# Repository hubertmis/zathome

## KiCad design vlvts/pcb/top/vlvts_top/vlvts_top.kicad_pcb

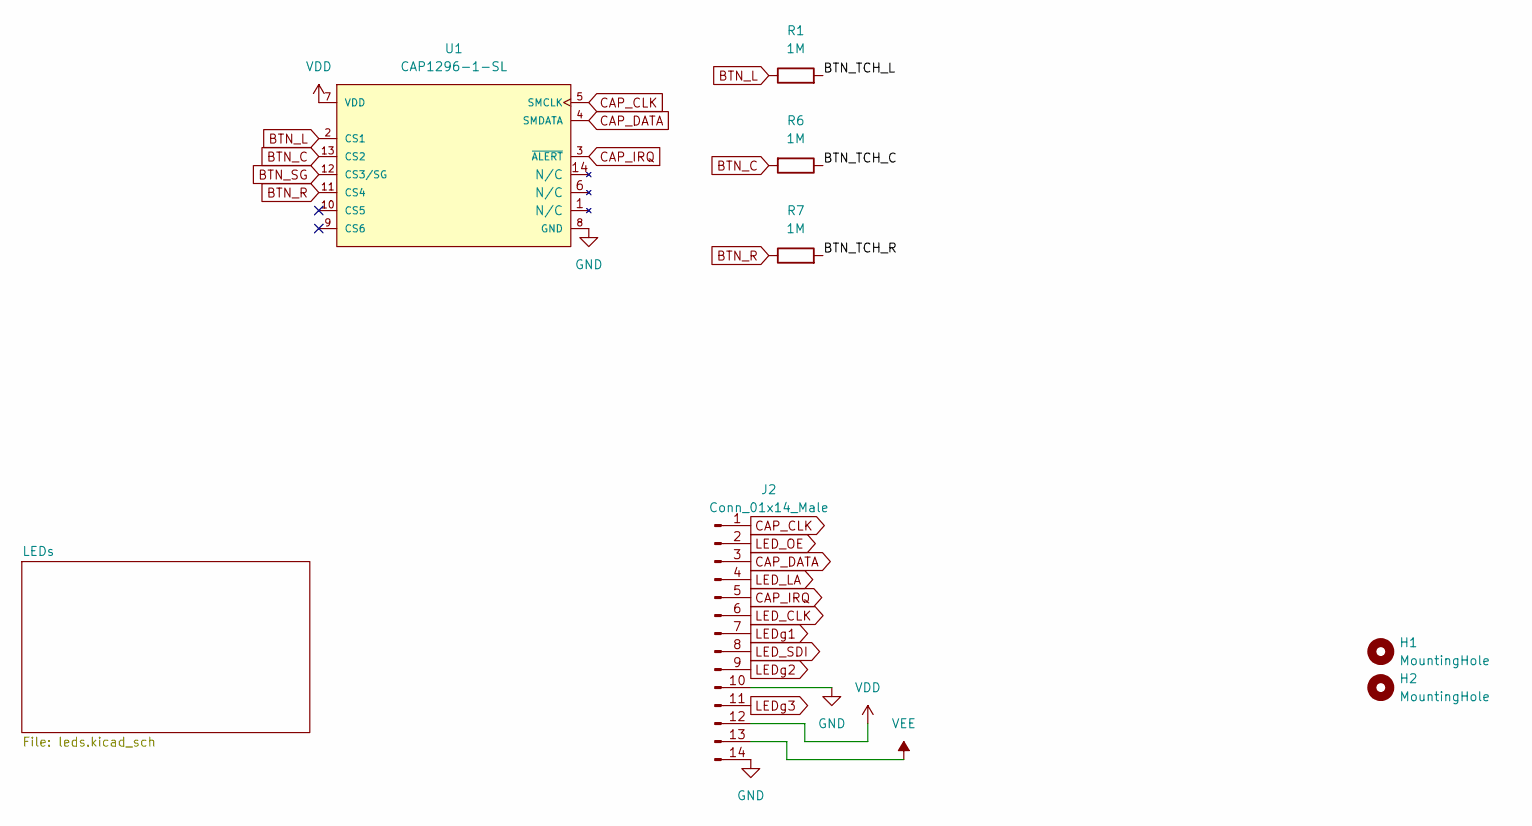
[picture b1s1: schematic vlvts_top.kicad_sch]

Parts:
H1, H2: MountingHole; MountingHole_3.2mm_M3_DIN965
J2: Conn_01x14_Male; PinHeader_2x07_P1.27mm_Vertical_SMD
R1, R6, R7: 1M; R_0603_1608Metric_Pad0.98x0.95mm_HandSolder
U1: CAP1296-1-SL; SOIC-14_3.9x8.7mm_P1.27mm

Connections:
/BTN_TCH_C: R6.1
/BTN_TCH_L: R1.2
/BTN_TCH_R: R7.2
BTN_C: R6.2, U1.13 (CS2)
BTN_L: R1.1, U1.2 (CS1)
BTN_R: R7.1, U1.11 (CS4)
BTN_SG: U1.12 (CS3/SG)
CAP_CLK: J2.1, U1.5 (SMCLK)
CAP_DATA: J2.3, U1.4 (SMDATA)
CAP_IRQ: J2.5, U1.3 (~ALERT)
GND: J2.10, J2.14, U1.8 (GND); also elsewhere on the board
LED_CLK: J2.6; also elsewhere on the board
LED_LA: J2.4; also elsewhere on the board
LED_OE: J2.2; also elsewhere on the board
LED_SDI: J2.8; also elsewhere on the board
LEDg1: J2.7; also elsewhere on the board
LEDg2: J2.9; also elsewhere on the board
LEDg3: J2.11; also elsewhere on the board
VDD: J2.12, U1.7 (VDD)
VEE: J2.13; also elsewhere on the board

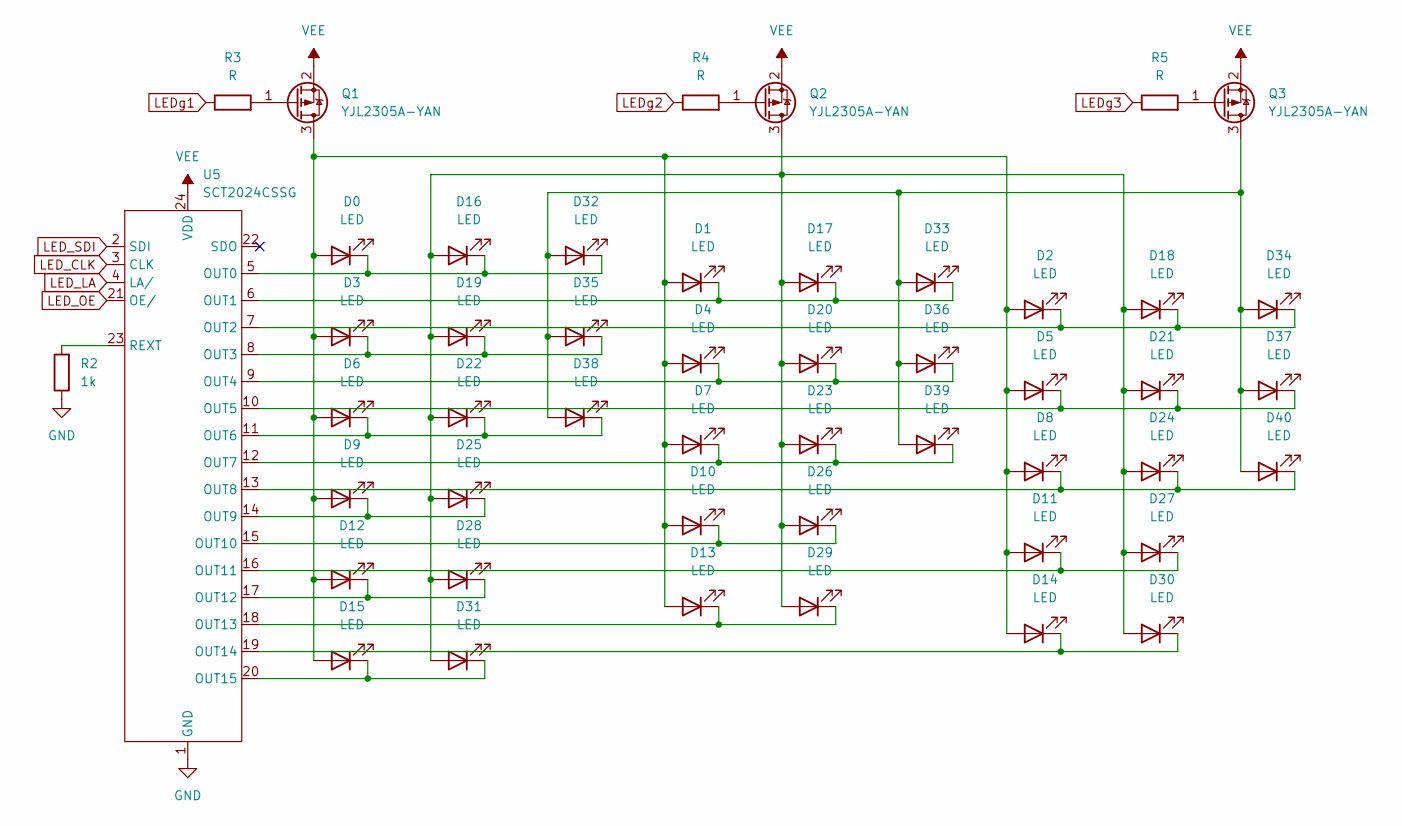
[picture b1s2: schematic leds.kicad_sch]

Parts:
D0, D1, D2, D3, D4, D5, D6, D7, D8, D9, D10, D11, D12, D13, D14, D15, D16, D17, D18, D19, D20, D21, D22, D23, D24, D25, D26, D27, D28, D29, D30, D31, D32, D33, D34, D35, D36, D37, D38, D39, D40: LED; LED_0603_1608Metric_Pad1.05x0.95mm_HandSolder
Q1, Q2, Q3: YJL2305A-YAN; SOT-23
R2: 1k; R_0603_1608Metric_Pad0.98x0.95mm_HandSolder
R3, R4, R5: R; R_0603_1608Metric_Pad0.98x0.95mm_HandSolder
U5: SCT2024CSSG; SSOP-24_3.9x8.7mm_P0.635mm

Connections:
GND: R2.1, U5.1 (GND); also elsewhere on the board
LED_CLK: U5.3 (CLK); also elsewhere on the board
LED_LA: U5.4 (LA/); also elsewhere on the board
LED_OE: U5.21 (OE/); also elsewhere on the board
LED_SDI: U5.2 (SDI); also elsewhere on the board
LEDg1: R3.1; also elsewhere on the board
LEDg2: R4.1; also elsewhere on the board
LEDg3: R5.1; also elsewhere on the board
unnamed: D0.2 (A), D1.2 (A), D2.2 (A), D3.2 (A), D4.2 (A), D5.2 (A), D6.2 (A), D7.2 (A), D8.2 (A), D9.2 (A), D10.2 (A), D11.2 (A), D12.2 (A), D13.2 (A), D14.2 (A), D15.2 (A), Q1.3 (D)
unnamed: D0.1 (K), D16.1 (K), D32.1 (K), U5.5 (OUT0)
unnamed: D1.1 (K), D17.1 (K), D33.1 (K), U5.6 (OUT1)
unnamed: D10.1 (K), D26.1 (K), U5.15 (OUT10)
unnamed: D11.1 (K), D27.1 (K), U5.16 (OUT11)
unnamed: D12.1 (K), D28.1 (K), U5.17 (OUT12)
unnamed: D13.1 (K), D29.1 (K), U5.18 (OUT13)
unnamed: D14.1 (K), D30.1 (K), U5.19 (OUT14)
unnamed: D15.1 (K), D31.1 (K), U5.20 (OUT15)
unnamed: D16.2 (A), D17.2 (A), D18.2 (A), D19.2 (A), D20.2 (A), D21.2 (A), D22.2 (A), D23.2 (A), D24.2 (A), D25.2 (A), D26.2 (A), D27.2 (A), D28.2 (A), D29.2 (A), D30.2 (A), D31.2 (A), Q2.3 (D)
unnamed: D2.1 (K), D18.1 (K), D34.1 (K), U5.7 (OUT2)
unnamed: D3.1 (K), D19.1 (K), D35.1 (K), U5.8 (OUT3)
unnamed: D4.1 (K), D20.1 (K), D36.1 (K), U5.9 (OUT4)
unnamed: D5.1 (K), D21.1 (K), D37.1 (K), U5.10 (OUT5)
unnamed: D6.1 (K), D22.1 (K), D38.1 (K), U5.11 (OUT6)
unnamed: D7.1 (K), D23.1 (K), D39.1 (K), U5.12 (OUT7)
unnamed: D8.1 (K), D24.1 (K), D40.1 (K), U5.13 (OUT8)
unnamed: D9.1 (K), D25.1 (K), U5.14 (OUT9)
unnamed: D32.2 (A), D33.2 (A), D34.2 (A), D35.2 (A), D36.2 (A), D37.2 (A), D38.2 (A), D39.2 (A), D40.2 (A), Q3.3 (D)
unnamed: Q1.1 (G), R3.2
unnamed: Q2.1 (G), R4.2
unnamed: Q3.1 (G), R5.2
unnamed: R2.2, U5.23 (REXT)
VEE: Q1.2 (S), Q2.2 (S), Q3.2 (S), U5.24 (VDD); also elsewhere on the board

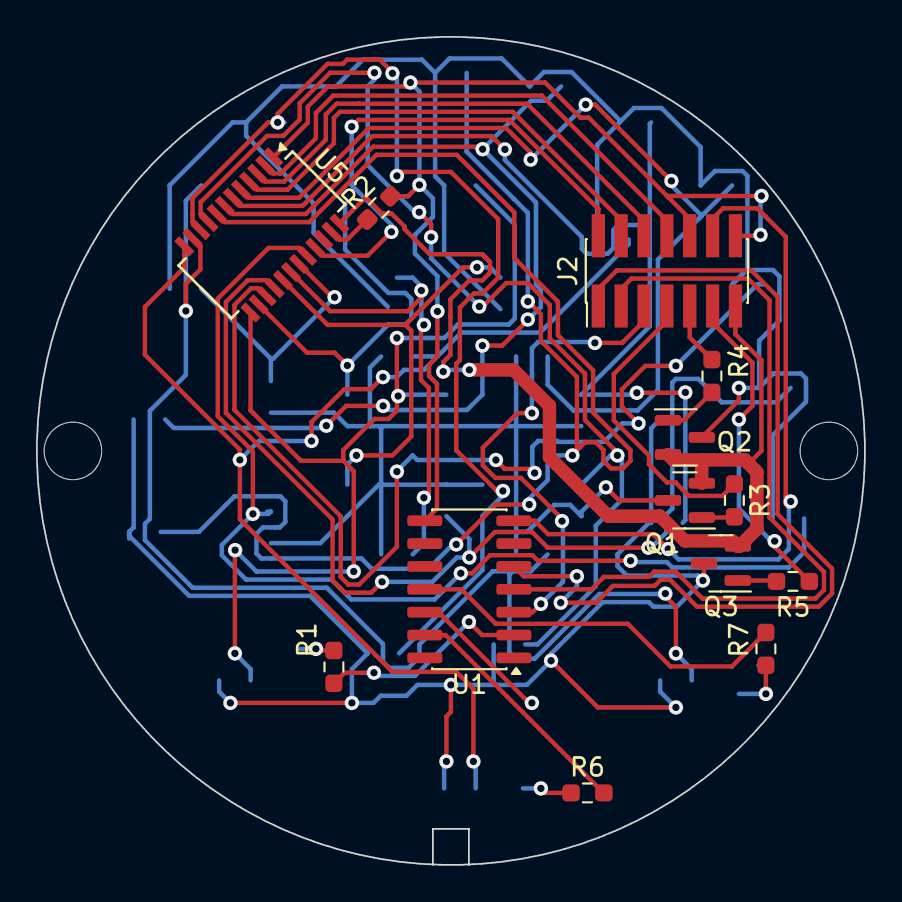
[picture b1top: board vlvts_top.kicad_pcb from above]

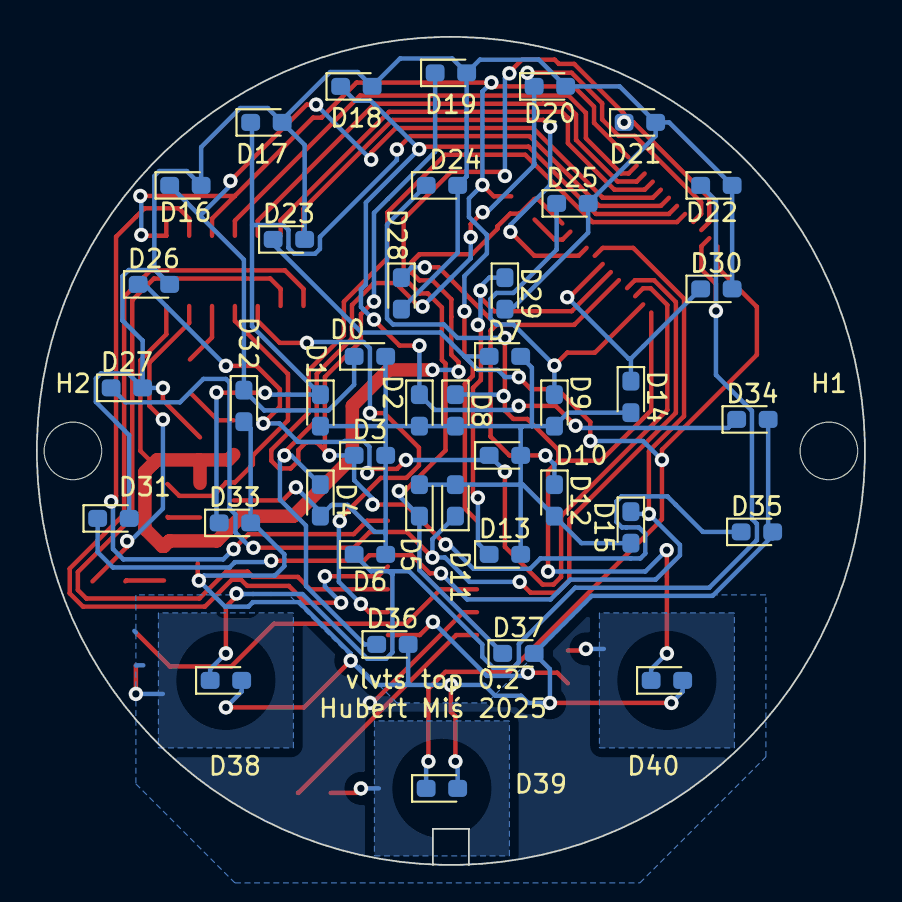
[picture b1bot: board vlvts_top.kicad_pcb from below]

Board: 2 copper layers, 46.0 x 46.0 mm, 56 parts (43 on the bottom side), 39 nets.

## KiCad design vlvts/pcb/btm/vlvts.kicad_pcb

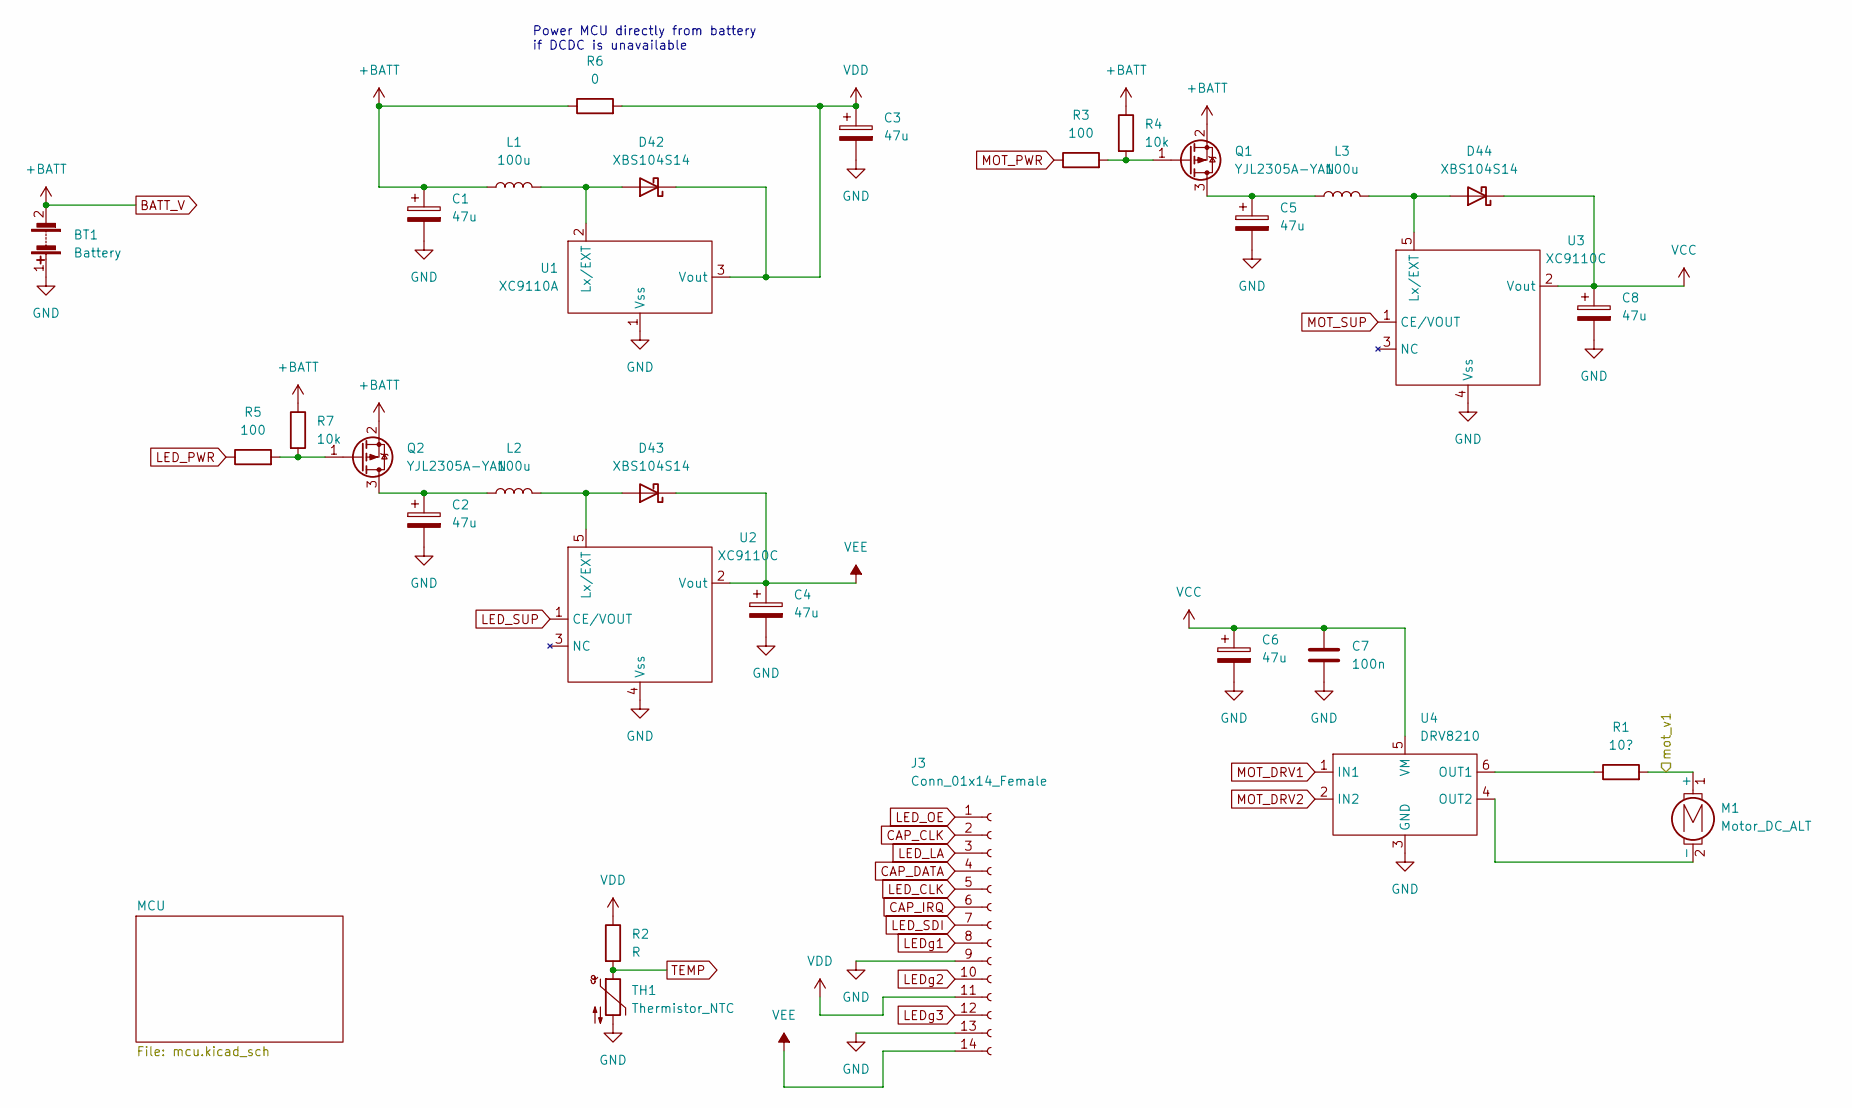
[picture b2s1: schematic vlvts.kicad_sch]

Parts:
BT1: Battery; JST_PH_B2B-PH-SM4-TB_1x02-1MP_P2.00mm_Vertical
C1, C2, C3, C4, C5, C6, C8: 47u; CP_EIA-6032-28_Kemet-C_Pad2.25x2.35mm_HandSolder
C7: 100n; C_0603_1608Metric_Pad1.08x0.95mm_HandSolder
D42, D43, D44: XBS104S14; D_SOD-123
J3: Conn_01x14_Female; PinHeader_2x07_P1.27mm_Vertical
L1, L2, L3: 100u; L_0805_2012Metric_Pad1.05x1.20mm_HandSolder
M1: Motor_DC_ALT; JST_PH_B2B-PH-SM4-TB_1x02-1MP_P2.00mm_Vertical
Q1, Q2: YJL2305A-YAN; SOT-23
R1: 10?; R_0805_2012Metric_Pad1.20x1.40mm_HandSolder
R2: R; R_0603_1608Metric_Pad0.98x0.95mm_HandSolder
R3, R5: 100; R_0603_1608Metric_Pad0.98x0.95mm_HandSolder
R4, R7: 10k; R_0603_1608Metric_Pad0.98x0.95mm_HandSolder
R6: 0; R_0603_1608Metric_Pad0.98x0.95mm_HandSolder
TH1: Thermistor_NTC; R_Axial_DIN0207_L6.3mm_D2.5mm_P2.54mm_Vertical
U1: XC9110A; SOT-23
U2, U3: XC9110C; SOT-23-5
U4: DRV8210; SOT-563

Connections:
/mot_v1: M1.1 (+), R1.2
BATT_V: BT1.2 (-), C1.1, L1.1, Q1.2 (S), Q2.2 (S), R4.1, R6.1, R7.1; also elsewhere on the board
CAP_CLK: J3.2; also elsewhere on the board
CAP_DATA: J3.4; also elsewhere on the board
CAP_IRQ: J3.6; also elsewhere on the board
GND: BT1.1 (+), C1.2, C2.2, C3.2, C4.2, C5.2, C6.2, C7.2, C8.2, J3.9, J3.13, TH1.2, U1.1 (Vss), U2.4 (Vss), U3.4 (Vss), U4.3 (GND); also elsewhere on the board
LED_CLK: J3.5; also elsewhere on the board
LED_LA: J3.3; also elsewhere on the board
LED_OE: J3.1; also elsewhere on the board
LED_PWR: R5.1; also elsewhere on the board
LED_SDI: J3.7; also elsewhere on the board
LED_SUP: U2.1 (CE/VOUT); also elsewhere on the board
LEDg1: J3.8; also elsewhere on the board
LEDg2: J3.10; also elsewhere on the board
LEDg3: J3.12; also elsewhere on the board
MOT_DRV1: U4.1 (IN1); also elsewhere on the board
MOT_DRV2: U4.2 (IN2); also elsewhere on the board
MOT_PWR: R3.1; also elsewhere on the board
MOT_SUP: U3.1 (CE/VOUT); also elsewhere on the board
unnamed: D42.2 (A), L1.2, U1.2 (Lx/EXT)
unnamed: D43.2 (A), L2.2, U2.5 (Lx/EXT)
unnamed: D44.2 (A), L3.2, U3.5 (Lx/EXT)
unnamed: M1.2 (-), U4.4 (OUT2)
unnamed: C5.1, L3.1, Q1.3 (D)
unnamed: Q1.1 (G), R3.2, R4.2
unnamed: C2.1, L2.1, Q2.3 (D)
unnamed: Q2.1 (G), R5.2, R7.2
unnamed: R1.1, U4.6 (OUT1)
TEMP: R2.2, TH1.1; also elsewhere on the board
VCC: C6.1, C7.1, C8.1, D44.1 (K), U3.2 (Vout), U4.5 (VM)
VDD: C3.1, D42.1 (K), J3.11, R2.1, R6.2, U1.3 (Vout); also elsewhere on the board
VEE: C4.1, D43.1 (K), J3.14, U2.2 (Vout)

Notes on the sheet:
Power MCU directly from battery if DCDC is unavailable

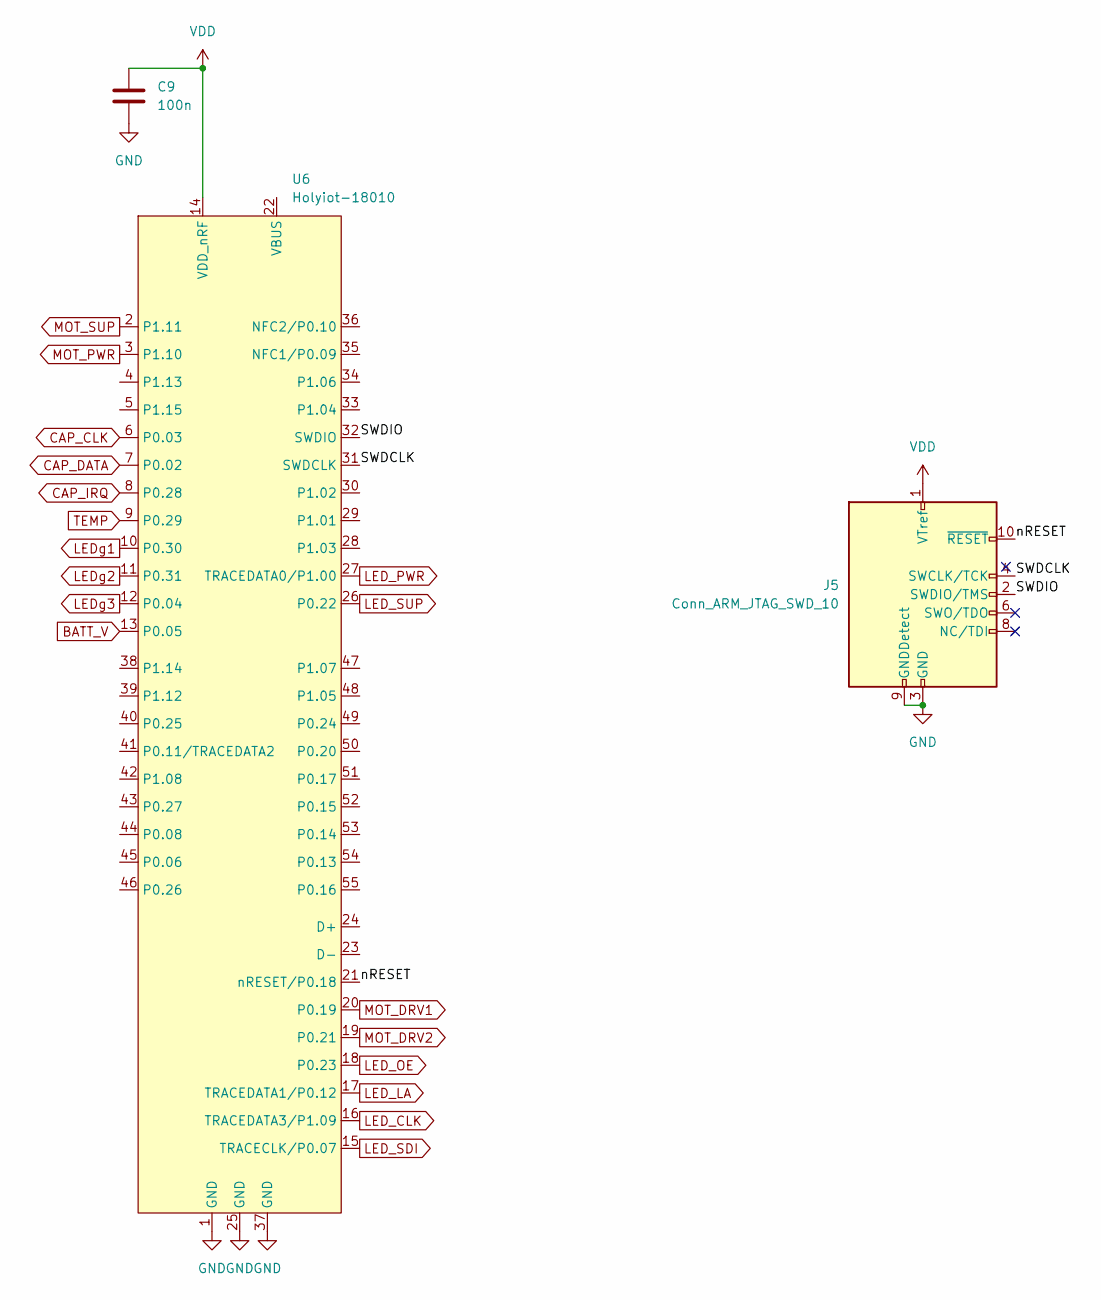
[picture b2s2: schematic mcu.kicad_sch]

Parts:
C9: 100n; C_0603_1608Metric_Pad1.08x0.95mm_HandSolder
J5: Conn_ARM_JTAG_SWD_10; Tag-Connect_TC2050-IDC-NL_2x05_P1.27mm_Vertical
U6: Holyiot-18010

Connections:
/MCU/SWDCLK: J5.4 (SWCLK/TCK), U6.31 (SWDCLK)
/MCU/SWDIO: J5.2 (SWDIO/TMS), U6.32 (SWDIO)
/MCU/nRESET: J5.10 (~RESET), U6.21 (nRESET/P0.18)
BATT_V: U6.13 (P0.05); also elsewhere on the board
CAP_CLK: U6.6 (P0.03); also elsewhere on the board
CAP_DATA: U6.7 (P0.02); also elsewhere on the board
CAP_IRQ: U6.8 (P0.28); also elsewhere on the board
GND: C9.2, J5.3 (GND), J5.5 (GND), J5.9 (GNDDetect), U6.1 (GND), U6.25 (GND), U6.37 (GND); also elsewhere on the board
LED_CLK: U6.16 (TRACEDATA3/P1.09); also elsewhere on the board
LED_LA: U6.17 (TRACEDATA1/P0.12); also elsewhere on the board
LED_OE: U6.18 (P0.23); also elsewhere on the board
LED_PWR: U6.27 (TRACEDATA0/P1.00); also elsewhere on the board
LED_SDI: U6.15 (TRACECLK/P0.07); also elsewhere on the board
LED_SUP: U6.26 (P0.22); also elsewhere on the board
LEDg1: U6.10 (P0.30); also elsewhere on the board
LEDg2: U6.11 (P0.31); also elsewhere on the board
LEDg3: U6.12 (P0.04); also elsewhere on the board
MOT_DRV1: U6.20 (P0.19); also elsewhere on the board
MOT_DRV2: U6.19 (P0.21); also elsewhere on the board
MOT_PWR: U6.3 (P1.10); also elsewhere on the board
MOT_SUP: U6.2 (P1.11); also elsewhere on the board
TEMP: U6.9 (P0.29); also elsewhere on the board
VDD: C9.1, J5.1 (VTref), U6.14 (VDD_nRF); also elsewhere on the board

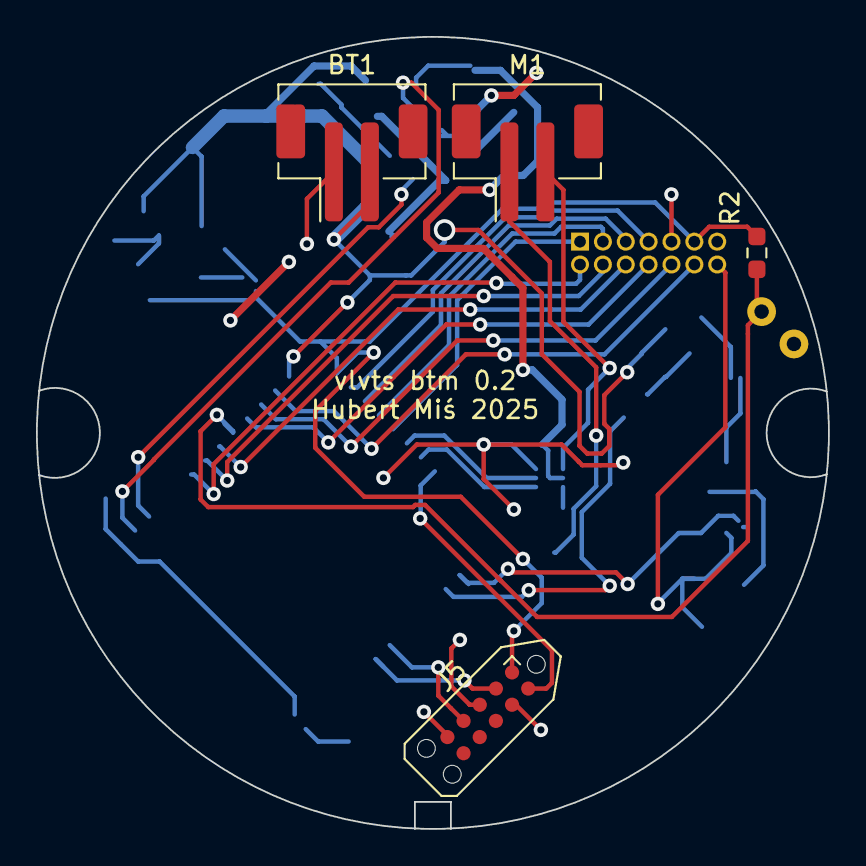
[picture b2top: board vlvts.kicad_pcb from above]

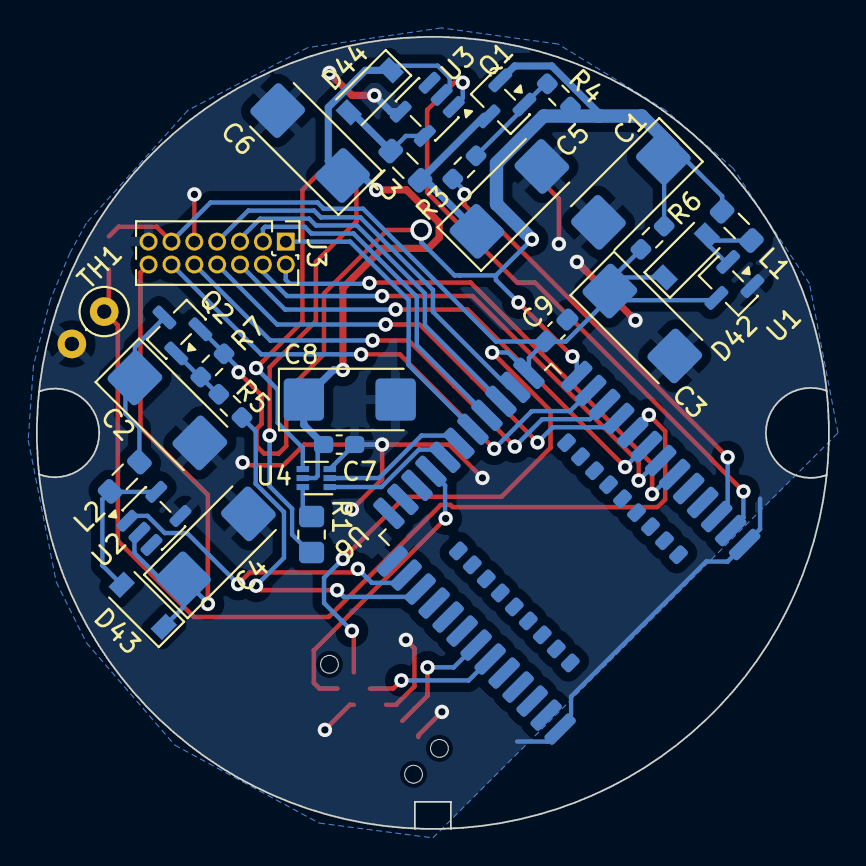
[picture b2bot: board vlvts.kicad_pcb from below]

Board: 2 copper layers, 44.0 x 44.0 mm, 34 parts (30 on the bottom side), 35 nets.

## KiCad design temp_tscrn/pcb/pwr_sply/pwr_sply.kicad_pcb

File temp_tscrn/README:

Build with:

$ west build -b temp_tscrn -- -DBOARD_ROOT=$PWD -DSB_CONFIG_BOOT_SIGNATURE_KEY_FILE=\"$PWD/temp_tscrn.pem\" -Dtemp_tscrn_COAPS_PSK=\"xxxx\"

or

$ west build -b nrf52840dk/nrf52840 -- -Dtemp_tscrn_COAPS_PSK=\"xxxx\"

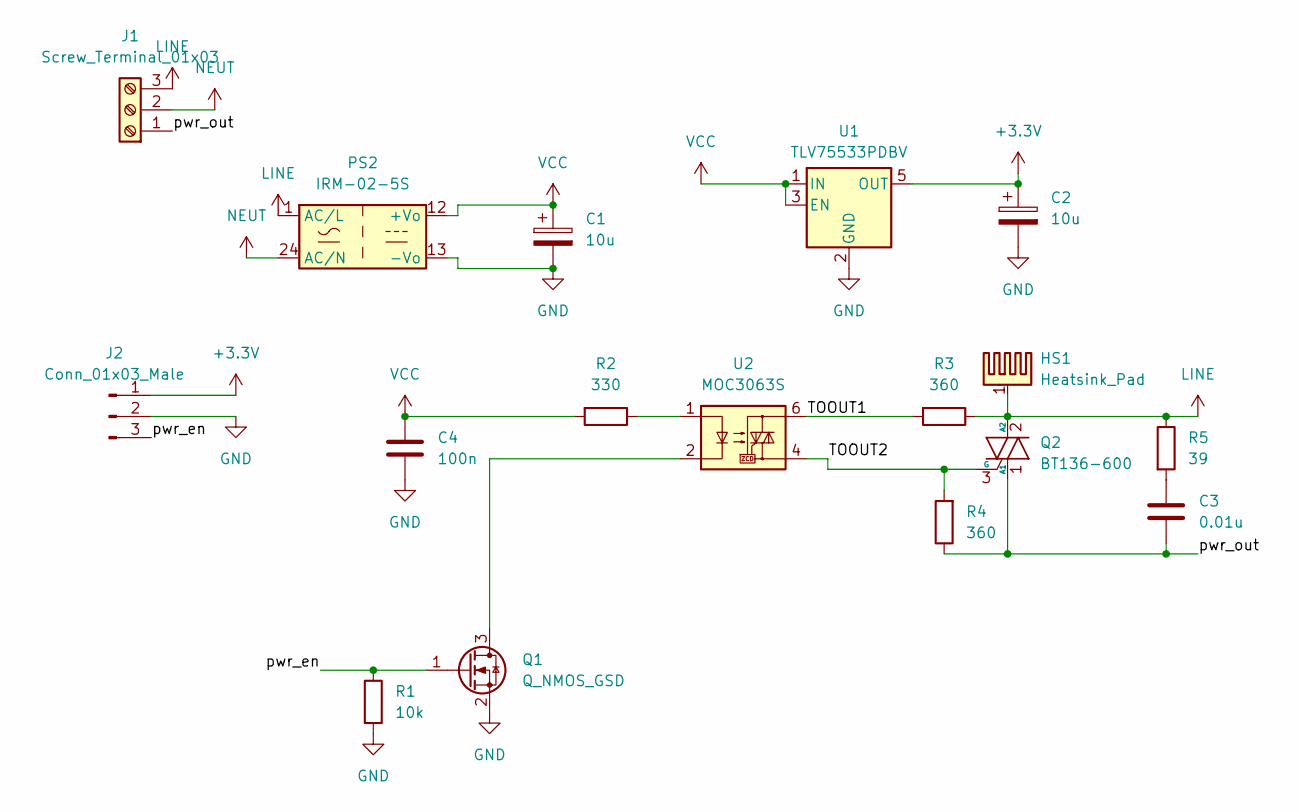
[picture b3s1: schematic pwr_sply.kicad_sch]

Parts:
C1, C2: 10u; CP_EIA-3216-18_Kemet-A_Pad1.58x1.35mm_HandSolder
C3: 0.01u; C_Rect_L10.0mm_W5.0mm_P5.00mm_P7.50mm
C4: 100n; C_0603_1608Metric_Pad1.08x0.95mm_HandSolder
HS1: Heatsink_Pad
J1: Screw_Terminal_01x03; TerminalBlock_MetzConnect_Type171_RT13703HBWC_1x03_P7.50mm_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
J2: Conn_01x03_Male; JST_PH_B3B-PH-K_1x03_P2.00mm_Vertical
PS2: IRM-02-5S; Converter_ACDC_MeanWell_IRM-02-xx_SMD
Q1: Q_NMOS_GSD; SOT-23
Q2: BT136-600; TO-252-2
R1: 10k; R_0603_1608Metric_Pad0.98x0.95mm_HandSolder
R2: 330; R_0603_1608Metric_Pad0.98x0.95mm_HandSolder
R3, R4: 360; R_0603_1608Metric_Pad0.98x0.95mm_HandSolder
R5: 39; R_0603_1608Metric_Pad0.98x0.95mm_HandSolder
U1: TLV75533PDBV; SOT-23-5
U2: MOC3063S; SMDIP-6_W7.62mm

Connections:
+3.3V: C2.1, J2.1, U1.5 (OUT)
/TOOUT1: R3.2, U2.6
/TOOUT2: Q2.3 (G), R4.2, U2.4
/pwr_en: J2.3, Q1.1 (G), R1.1
/pwr_out: C3.2, J1.1, Q2.1 (A1), R4.1
GND: C1.2, C2.2, C4.2, J2.2, PS2.13 (-Vo), Q1.2 (S), R1.2, U1.2 (GND)
LINE: HS1.1, J1.3, PS2.1 (AC/L), Q2.2 (A2), R3.1, R5.1
NEUT: J1.2, PS2.24 (AC/N)
unnamed: C3.1, R5.2
unnamed: Q1.3 (D), U2.2
unnamed: R2.1, U2.1
VCC: C1.1, C4.1, PS2.12 (+Vo), R2.2, U1.1 (IN), U1.3 (EN)

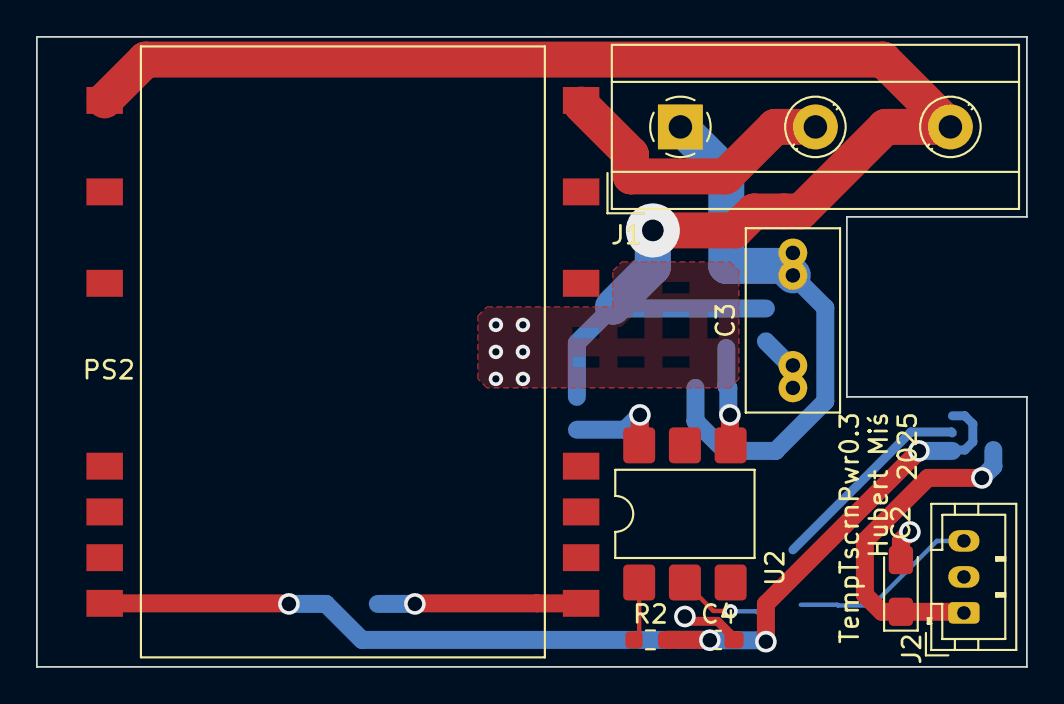
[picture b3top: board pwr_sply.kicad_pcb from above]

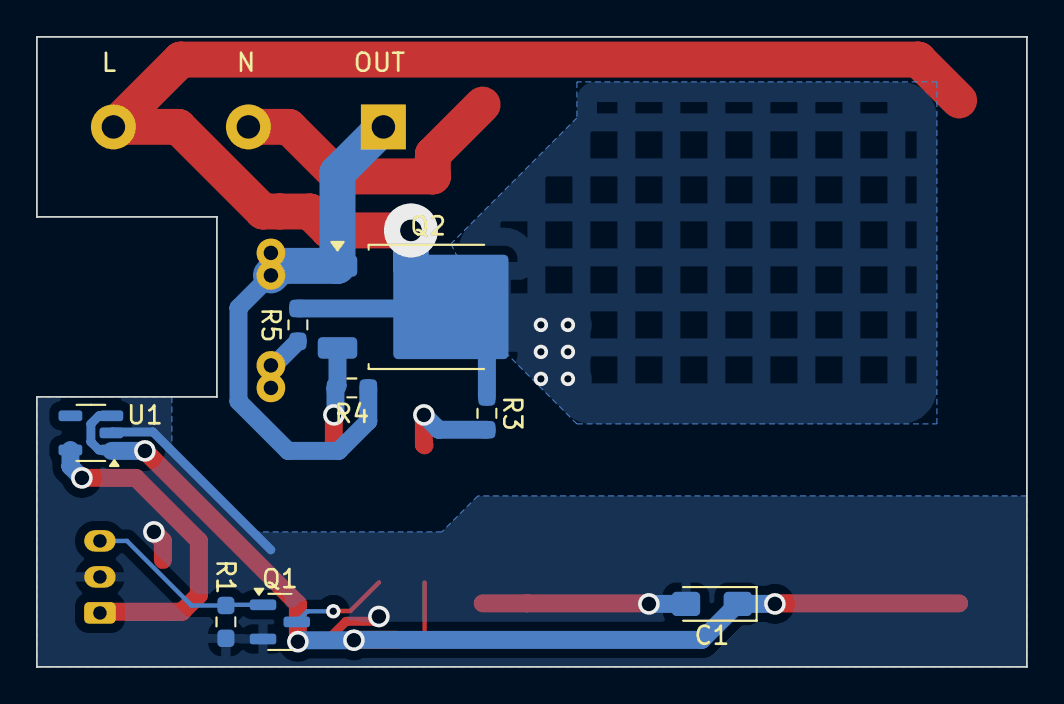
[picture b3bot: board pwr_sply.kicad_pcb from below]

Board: 2 copper layers, 55.0 x 35.0 mm, 16 parts (8 on the bottom side), 12 nets.

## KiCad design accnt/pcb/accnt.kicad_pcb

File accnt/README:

Build with:

$ west build -b accnt -- -Dmcuboot_OVERLAY_CONFIG=$PWD/mcuboot_prj.conf -Dmcuboot_CONF_DIR=$PWD -Dmcuboot_key_file=$PWD/mykey.pem -DCOAPS_PSK=\"xxxx\"

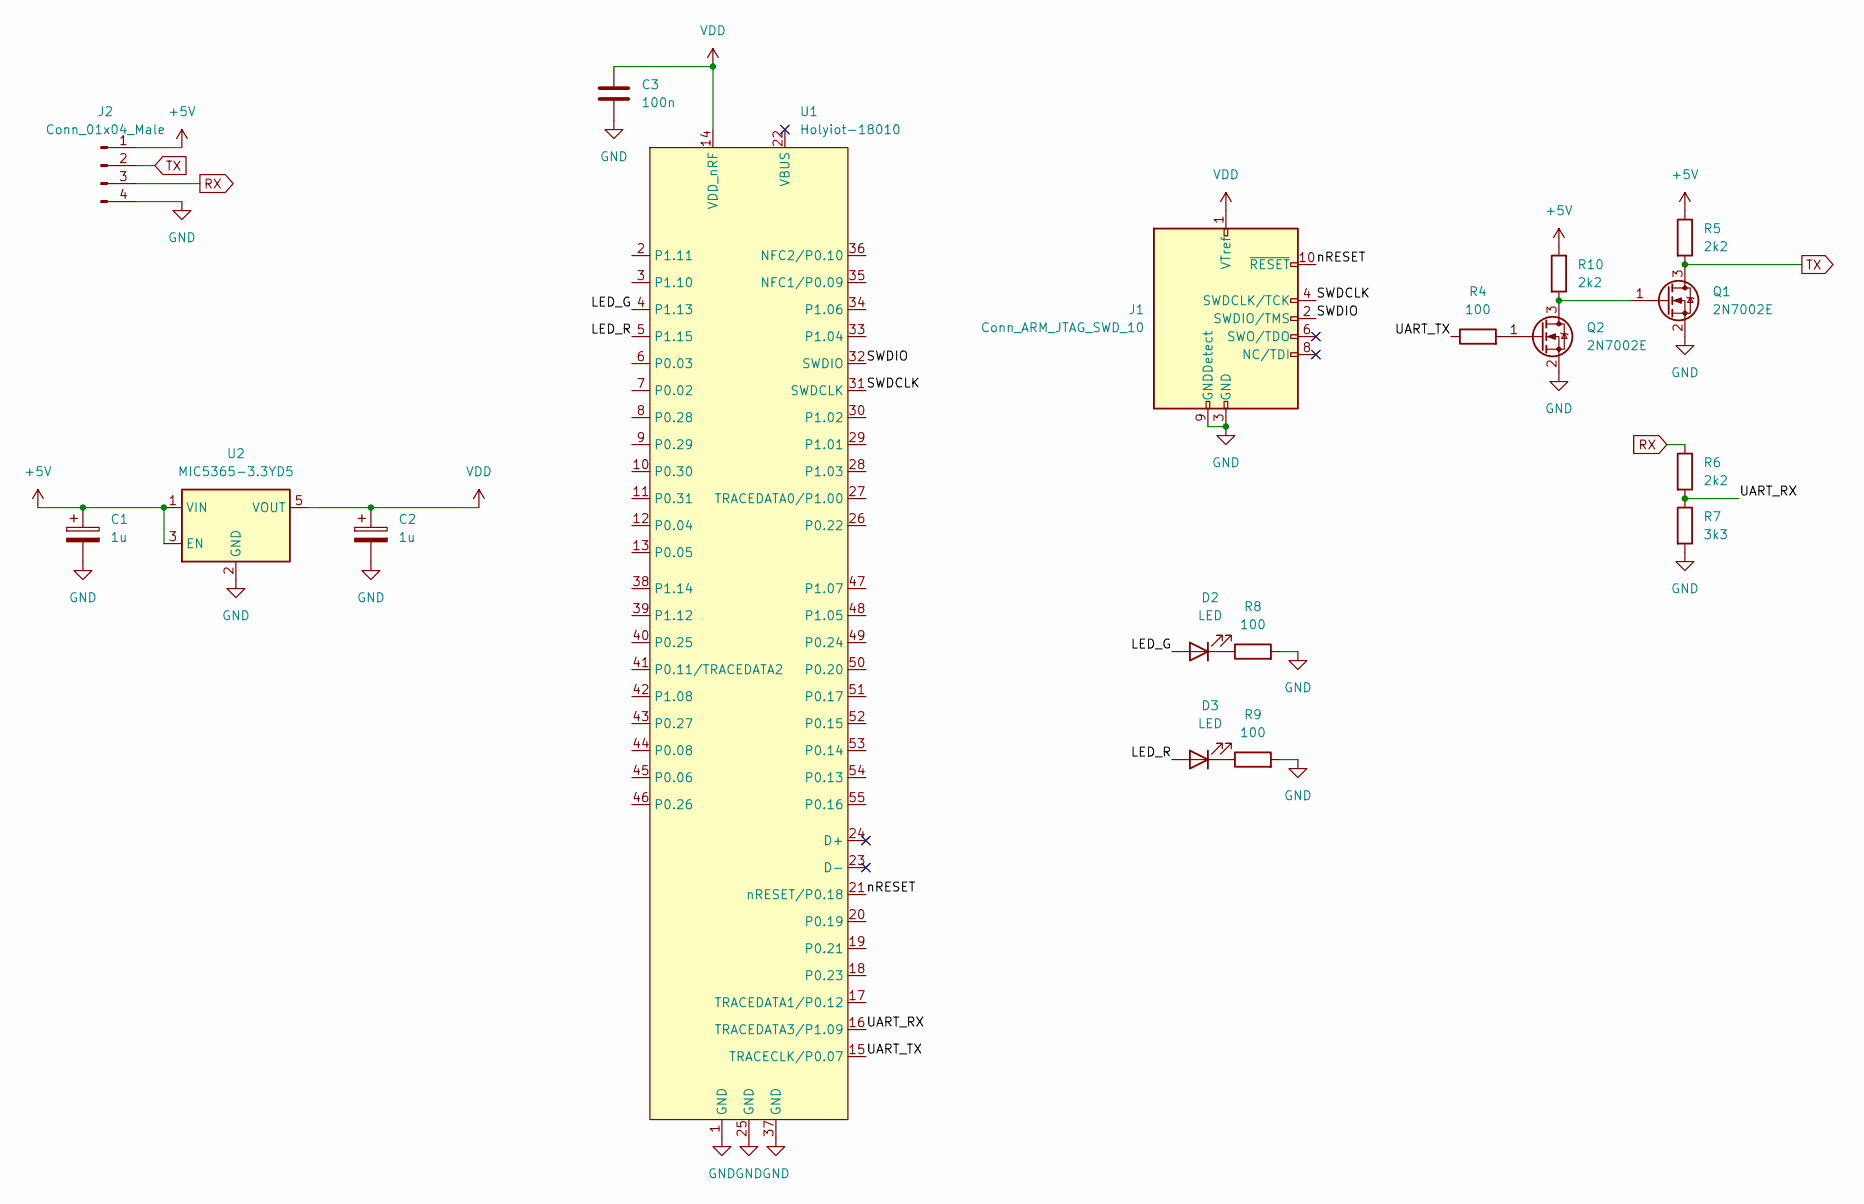
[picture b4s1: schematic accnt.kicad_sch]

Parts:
C1, C2: 1u; CP_EIA-3216-18_Kemet-A_Pad1.58x1.35mm_HandSolder
C3: 100n; C_0603_1608Metric_Pad1.08x0.95mm_HandSolder
D2, D3: LED; LED_0603_1608Metric_Pad1.05x0.95mm_HandSolder
J1: Conn_ARM_JTAG_SWD_10; PinHeader_2x05_P1.27mm_Vertical_SMD
J2: Conn_01x04_Male; JST_ZE_SM04B-ZESS-TB_1x04-1MP_P1.50mm_Horizontal
Q1, Q2: 2N7002E; SOT-23
R4, R8, R9: 100; R_0603_1608Metric_Pad0.98x0.95mm_HandSolder
R5, R6, R10: 2k2; R_0603_1608Metric_Pad0.98x0.95mm_HandSolder
R7: 3k3; R_0603_1608Metric_Pad0.98x0.95mm_HandSolder
U1: Holyiot-18010
U2: MIC5365-3.3YD5; SOT-23-5

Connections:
+5V: C1.1, J2.1, R5.1, R10.1, U2.1 (VIN), U2.3 (EN)
/LED_G: D2.2 (A), U1.4 (P1.13)
/LED_R: D3.2 (A), U1.5 (P1.15)
/SWDCLK: J1.4 (SWDCLK/TCK), U1.31 (SWDCLK)
/SWDIO: J1.2 (SWDIO/TMS), U1.32 (SWDIO)
/UART_RX: R6.2, R7.1, U1.16 (TRACEDATA3/P1.09)
/UART_TX: R4.1, U1.15 (TRACECLK/P0.07)
/nRESET: J1.10 (~RESET), U1.21 (nRESET/P0.18)
GND: C1.2, C2.2, C3.2, J1.3 (GND), J1.5 (GND), J1.9 (GNDDetect), J2.4, Q1.2 (S), Q2.2 (S), R7.2, R8.2, R9.2, U1.1 (GND), U1.25 (GND), U1.37 (GND), U2.2 (GND)
unnamed: D2.1 (K), R8.1
unnamed: D3.1 (K), R9.1
unnamed: Q1.1 (G), Q2.3 (D), R10.2
unnamed: Q2.1 (G), R4.2
RX: J2.3, R6.1
TX: J2.2, Q1.3 (D), R5.2
VDD: C2.1, C3.1, J1.1 (VTref), U1.14 (VDD_nRF), U2.5 (VOUT)

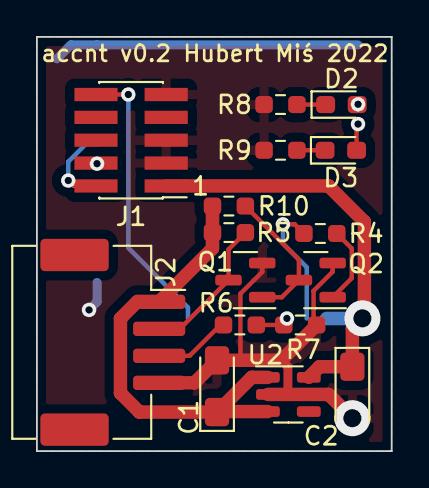
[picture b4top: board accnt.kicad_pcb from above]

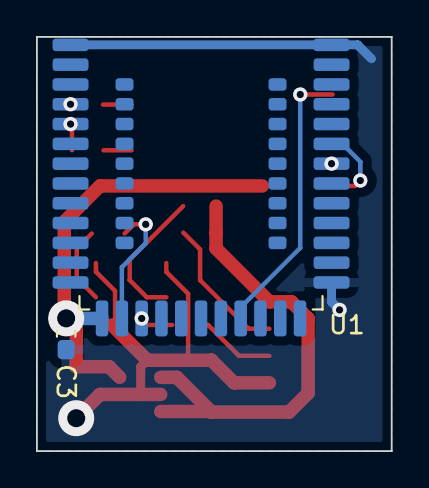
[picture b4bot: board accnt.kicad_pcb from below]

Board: 2 copper layers, 19.7 x 23.0 mm, 18 parts (2 on the bottom side), 16 nets.
